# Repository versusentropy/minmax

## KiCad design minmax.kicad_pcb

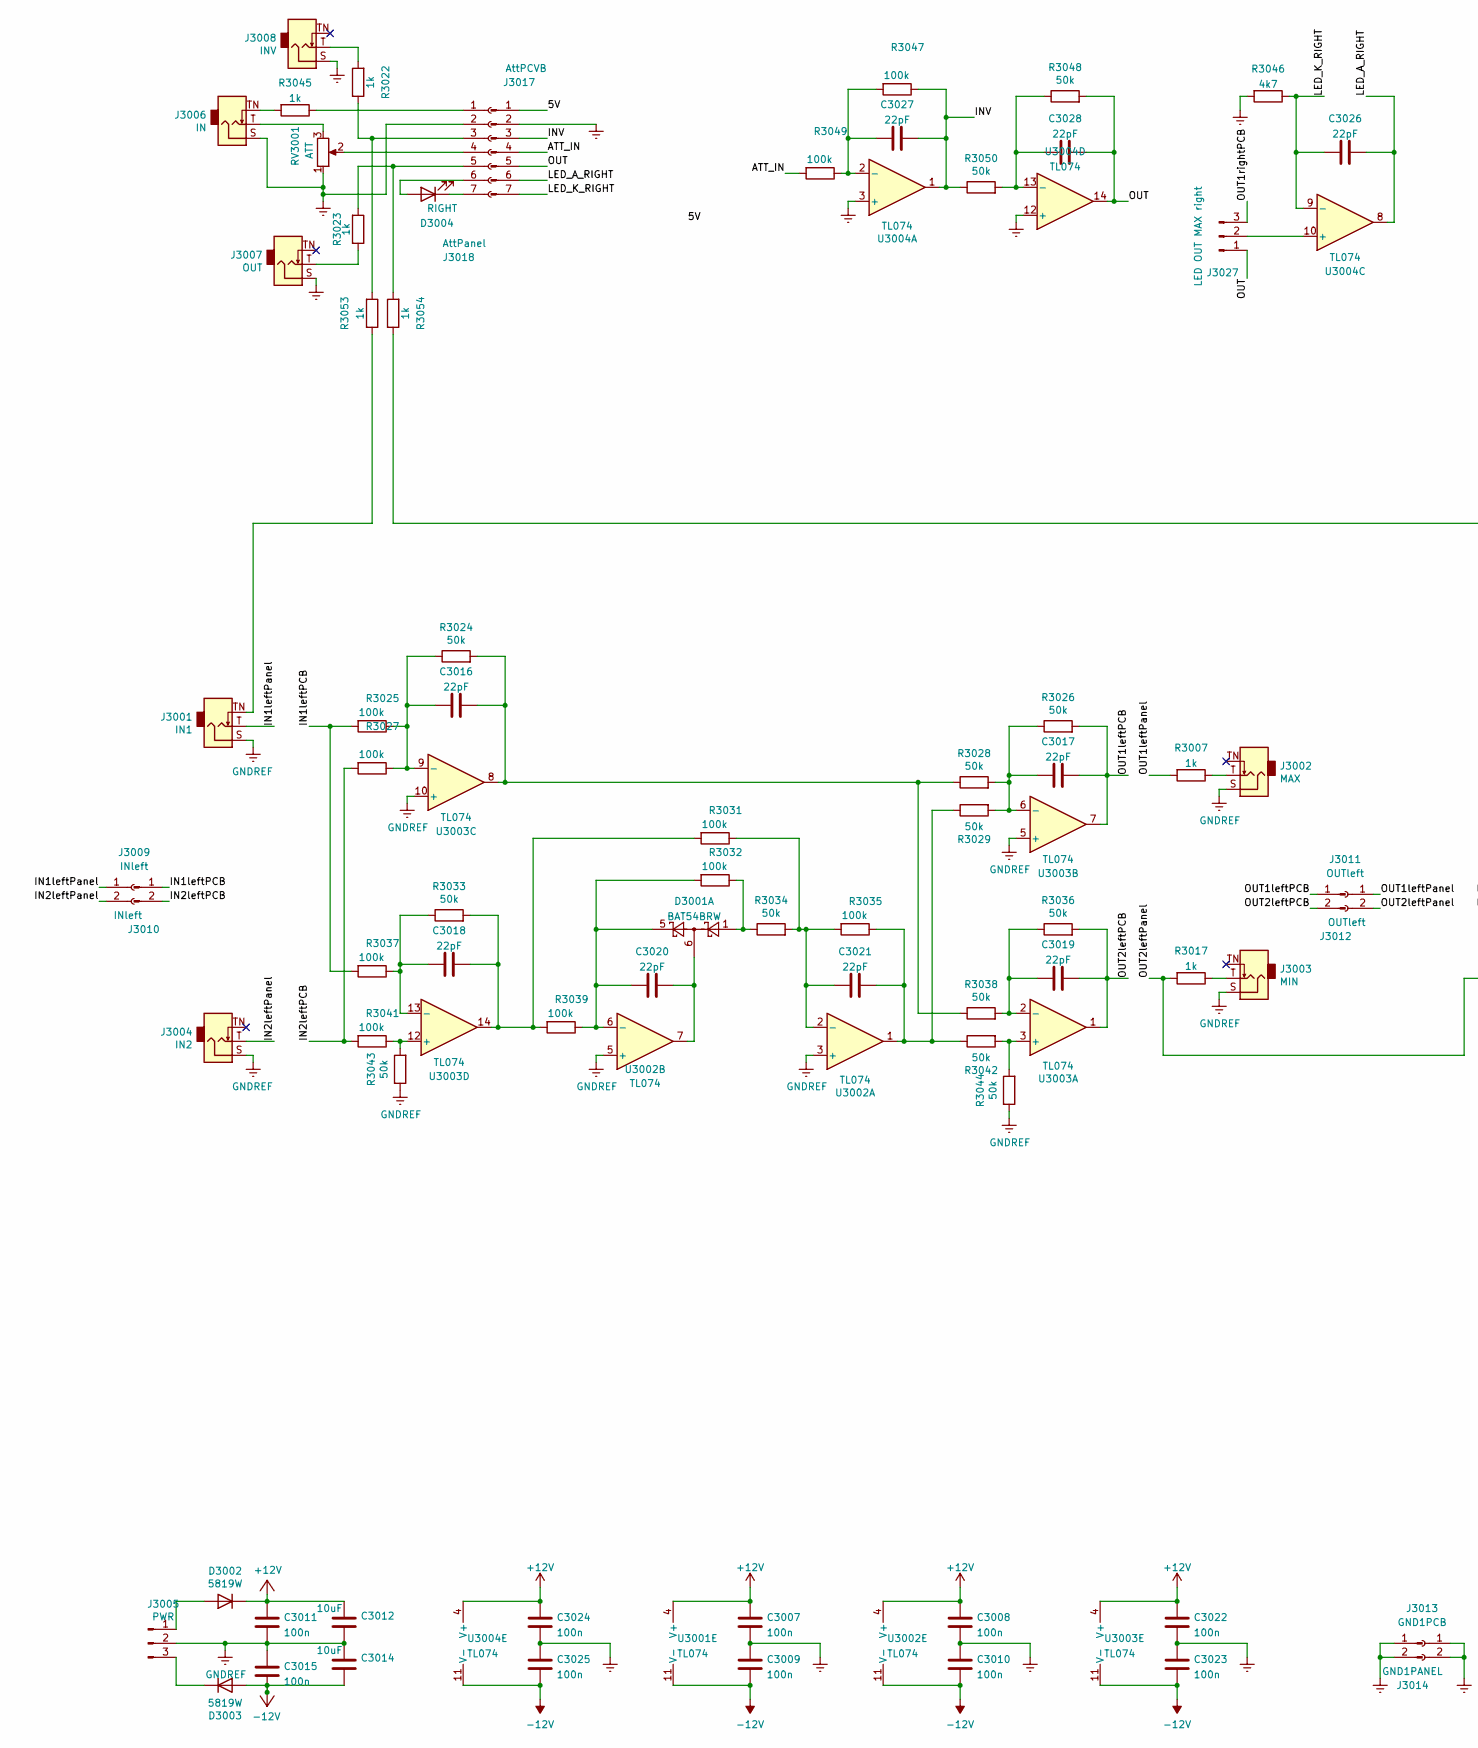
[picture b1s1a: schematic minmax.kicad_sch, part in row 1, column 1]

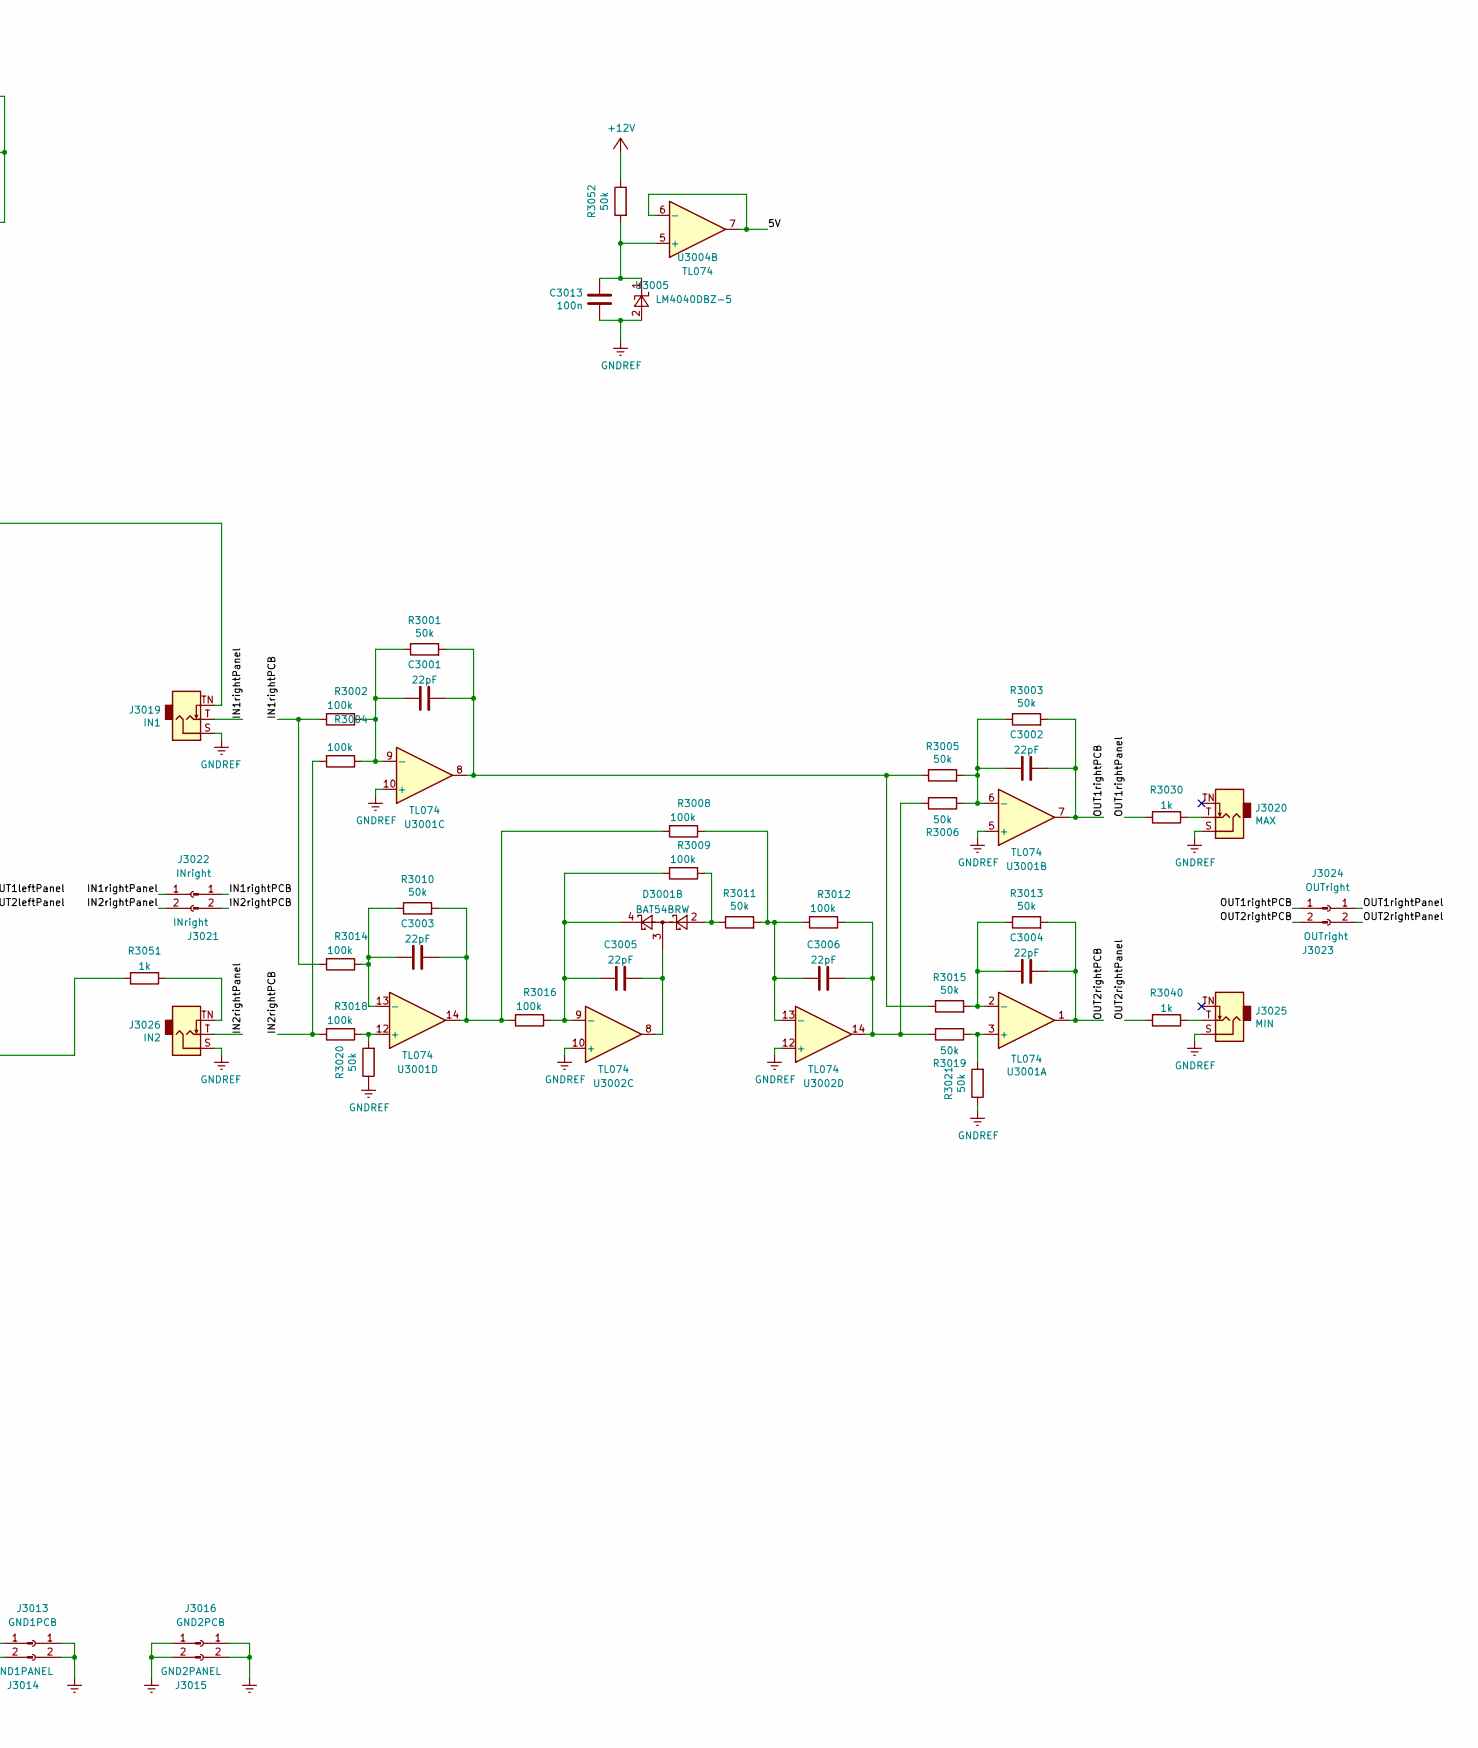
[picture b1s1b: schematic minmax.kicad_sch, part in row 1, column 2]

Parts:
C3001, C3002, C3003, C3004, C3005, C3006, C3016, C3017, C3018, C3019, C3020, C3021, C3026, C3027, C3028: 22pF; C_0402_1005Metric; LCSC C1555
C3007, C3008, C3009, C3010, C3011, C3013, C3015, C3022, C3023, C3024, C3025: 100n; C_0402_1005Metric; LCSC C307331
C3012, C3014: 10uF; C_0805_2012Metric; LCSC C15850
D3001: BAT54BRW; SOT-363_SC-70-6; LCSC C124897
D3002, D3003: 5819W; D_SOD-123; LCSC C8598
D3004: RIGHT; LED_D3.0mm
J3001, J3019: IN1; Jack_3.5mm_QingPu_WQP-PJ398SM_Vertical_CircularHolesSMALL
J3002, J3020: MAX; Jack_3.5mm_QingPu_WQP-PJ398SM_Vertical_CircularHolesSMALL
J3003, J3025: MIN; Jack_3.5mm_QingPu_WQP-PJ398SM_Vertical_CircularHolesSMALL
J3004, J3026: IN2; Jack_3.5mm_QingPu_WQP-PJ398SM_Vertical_CircularHolesSMALL
J3005: PWR; eurorac_power-v2
J3006: IN; Jack_3.5mm_QingPu_WQP-PJ398SM_Vertical_CircularHolesSMALL
J3007: OUT; Jack_3.5mm_QingPu_WQP-PJ398SM_Vertical_CircularHolesSMALL
J3008: INV; Jack_3.5mm_QingPu_WQP-PJ398SM_Vertical_CircularHolesSMALL
J3009: INleft; PinHeader_1x02_P2.54mm_Vertical
J3010: INleft; PinSocket_1x02_P2.54mm_Vertical
J3011: OUTleft; PinHeader_1x02_P2.54mm_Vertical
J3012: OUTleft; PinSocket_1x02_P2.54mm_Vertical
J3013: GND1PCB; PinHeader_1x02_P2.54mm_Vertical
J3014: GND1PANEL; PinSocket_1x02_P2.54mm_Vertical
J3015: GND2PANEL; PinSocket_1x02_P2.54mm_Vertical
J3016: GND2PCB; PinHeader_1x02_P2.54mm_Vertical
J3017: AttPCVB; PinHeader_1x07_P2.54mm_Vertical
J3018: AttPanel; PinSocket_1x07_P2.54mm_Vertical
J3021: INright; PinSocket_1x02_P2.54mm_Vertical
J3022: INright; PinHeader_1x02_P2.54mm_Vertical
J3023: OUTright; PinSocket_1x02_P2.54mm_Vertical
J3024: OUTright; PinHeader_1x02_P2.54mm_Vertical
J3027: LED OUT MAX right; PinHeader_1x03_P2.54mm_Vertical
R3001, R3003, R3005, R3006, R3010, R3011, R3013, R3015, R3019, R3020, R3021, R3024, R3026, R3028, R3029, R3033, R3034, R3036, R3038, R3042, R3043, R3044, R3048, R3050, R3052: 50k; R_0402_1005Metric; LCSC C25897
R3002, R3004, R3008, R3009, R3012, R3014, R3016, R3018, R3025, R3027, R3031, R3032, R3035, R3037, R3039, R3041, R3047, R3049: 100k; R_0402_1005Metric; LCSC C25741
R3007, R3017, R3022, R3023, R3030, R3040, R3045, R3051, R3053, R3054: 1k; R_0603_1608Metric; LCSC C21190
R3046: 4k7; R_0603_1608Metric; LCSC C23162
RV3001: ATT; RD901F-ALPHA-POT
U3001, U3002, U3003, U3004: TL074; TSSOP-14_4.4x5mm_P0.65mm; LCSC C96507
U3005: LM4040DBZ-5; SOT-23; LCSC C202168

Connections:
+12V: C3007.1, C3008.1, C3011.1, C3012.1, C3022.1, C3024.1, D3002.1 (K), R3052.1, U3001.4 (V+), U3002.4 (V+), U3003.4 (V+), U3004.4 (V+)
-12V: C3009.2, C3010.2, C3014.2, C3015.2, C3023.2, C3025.2, D3003.2 (A), U3001.11 (V-), U3002.11 (V-), U3003.11 (V-), U3004.11 (V-)
/5V: J3017.1, U3004.6 (-), U3004.7
/ATT_IN: J3017.4, R3049.2
/IN1leftPCB: J3009.1, R3025.2, R3037.2
/IN1leftPanel: J3001.T, J3010.1
/IN1rightPCB: J3022.1, R3002.2, R3014.2
/IN1rightPanel: J3019.T, J3021.1
/IN2leftPCB: J3009.2, R3027.2, R3041.2
/IN2leftPanel: J3004.T, J3010.2
/IN2rightPCB: J3022.2, R3004.2, R3018.2
/IN2rightPanel: J3021.2, J3026.T
/INV: C3027.2, J3017.3, R3047.1, R3050.1, U3004.1
/LED_A_RIGHT: C3026.2, J3017.6, U3004.8
/LED_K_RIGHT: C3026.1, J3017.7, R3046.1, U3004.9 (-)
/OUT: C3028.2, J3017.5, J3027.1, R3048.2, U3004.14
/OUT1leftPCB: C3017.2, J3011.1, R3026.2, U3003.7
/OUT1leftPanel: J3012.1, R3007.2
/OUT1rightPCB: C3002.2, J3024.1, J3027.3, R3003.2, U3001.7
/OUT1rightPanel: J3023.1, R3030.2
/OUT2leftPCB: C3019.2, J3011.2, R3036.2, U3003.1
/OUT2leftPanel: J3012.2, R3017.2, R3051.2
/OUT2rightPCB: C3004.2, J3024.2, R3013.2, U3001.1
/OUT2rightPanel: J3023.2, R3040.2
GNDREF: C3007.2, C3008.2, C3009.1, C3010.1, C3011.2, C3012.2, C3013.1, C3014.1, C3015.1, C3022.2, C3023.1, C3024.2, C3025.1, J3001.S, J3002.S, J3003.S, J3004.S, J3005.2, J3006.S, J3007.S, J3008.S, J3013.1, J3013.2, J3014.1, J3014.2, J3015.1, J3015.2, J3016.1, J3016.2, J3017.2, J3018.2, J3019.S, J3020.S, J3025.S, J3026.S, R3020.1, R3021.1, R3043.1, R3044.1, R3046.2, RV3001.1, U3001.5 (+), U3001.10 (+), U3002.3 (+), U3002.5 (+), U3002.10 (+), U3002.12 (+), U3003.5 (+), U3003.10 (+), U3004.3 (+), U3004.12 (+), U3005.2 (A)
unnamed: C3001.1, R3001.1, R3002.1, R3004.1, U3001.9 (-)
unnamed: C3001.2, R3001.2, R3005.1, R3015.1, U3001.8
unnamed: C3002.1, R3003.1, R3005.2, R3006.2, U3001.6 (-)
unnamed: C3003.1, R3010.1, R3014.1, U3001.13 (-)
unnamed: C3003.2, R3008.2, R3010.2, R3016.2, U3001.14
unnamed: C3004.1, R3013.1, R3015.2, U3001.2 (-)
unnamed: C3005.1, D3001.4, R3009.2, R3016.1, U3002.9 (-)
unnamed: C3005.2, D3001.3, U3002.8
unnamed: C3006.1, R3008.1, R3011.2, R3012.2, U3002.13 (-)
unnamed: C3006.2, R3006.1, R3012.1, R3019.1, U3002.14
unnamed: C3013.2, R3052.2, U3004.5 (+), U3005.1 (K)
unnamed: C3016.1, R3024.1, R3025.1, R3027.1, U3003.9 (-)
unnamed: C3016.2, R3024.2, R3028.1, R3038.1, U3003.8
unnamed: C3017.1, R3026.1, R3028.2, R3029.2, U3003.6 (-)
unnamed: C3018.1, R3033.1, R3037.1, U3003.13 (-)
unnamed: C3018.2, R3031.2, R3033.2, R3039.2, U3003.14
unnamed: C3019.1, R3036.1, R3038.2, U3003.2 (-)
unnamed: C3020.1, D3001.5, R3032.2, R3039.1, U3002.6 (-)
unnamed: C3020.2, D3001.6, U3002.7
unnamed: C3021.1, R3031.1, R3034.2, R3035.2, U3002.2 (-)
unnamed: C3021.2, R3029.1, R3035.1, R3042.1, U3002.1
unnamed: C3027.1, R3047.2, R3049.1, U3004.2 (-)
unnamed: C3028.1, R3048.1, R3050.2, U3004.13 (-)
unnamed: D3001.1, R3032.1, R3034.1
unnamed: D3001.2, R3009.1, R3011.1
unnamed: D3002.2 (A), J3005.1
unnamed: D3003.1 (K), J3005.3
unnamed: D3004.1 (K), J3018.7
unnamed: D3004.2 (A), J3018.6
unnamed: J3001.TN, R3053.1
unnamed: J3002.T, R3007.1
unnamed: J3003.T, R3017.1
unnamed: J3006.T, RV3001.3
unnamed: J3006.TN, R3045.2
unnamed: J3007.T, R3023.1
unnamed: J3008.T, R3022.2
unnamed: J3018.1, R3045.1
unnamed: J3018.3, R3022.1, R3053.2
unnamed: J3018.4, RV3001.2
unnamed: J3018.5, R3023.2, R3054.2
unnamed: J3019.TN, R3054.1
unnamed: J3020.T, R3030.1
unnamed: J3025.T, R3040.1
unnamed: J3026.TN, R3051.1
unnamed: J3027.2, U3004.10 (+)
unnamed: R3018.1, R3020.2, U3001.12 (+)
unnamed: R3019.2, R3021.2, U3001.3 (+)
unnamed: R3041.1, R3043.2, U3003.12 (+)
unnamed: R3042.2, R3044.2, U3003.3 (+)

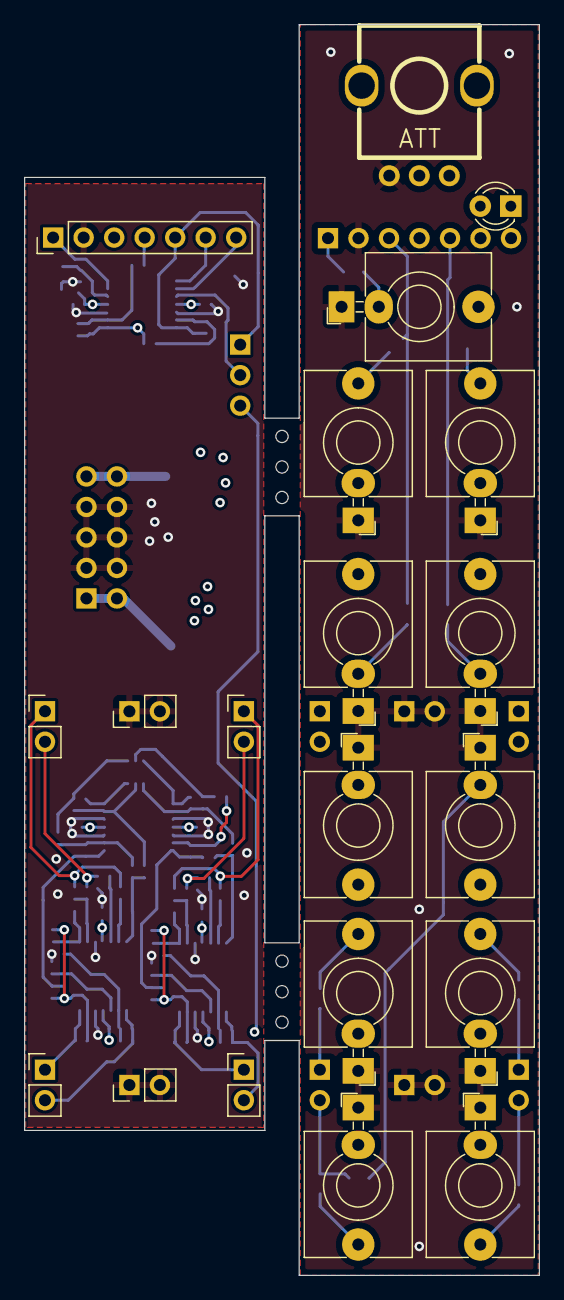
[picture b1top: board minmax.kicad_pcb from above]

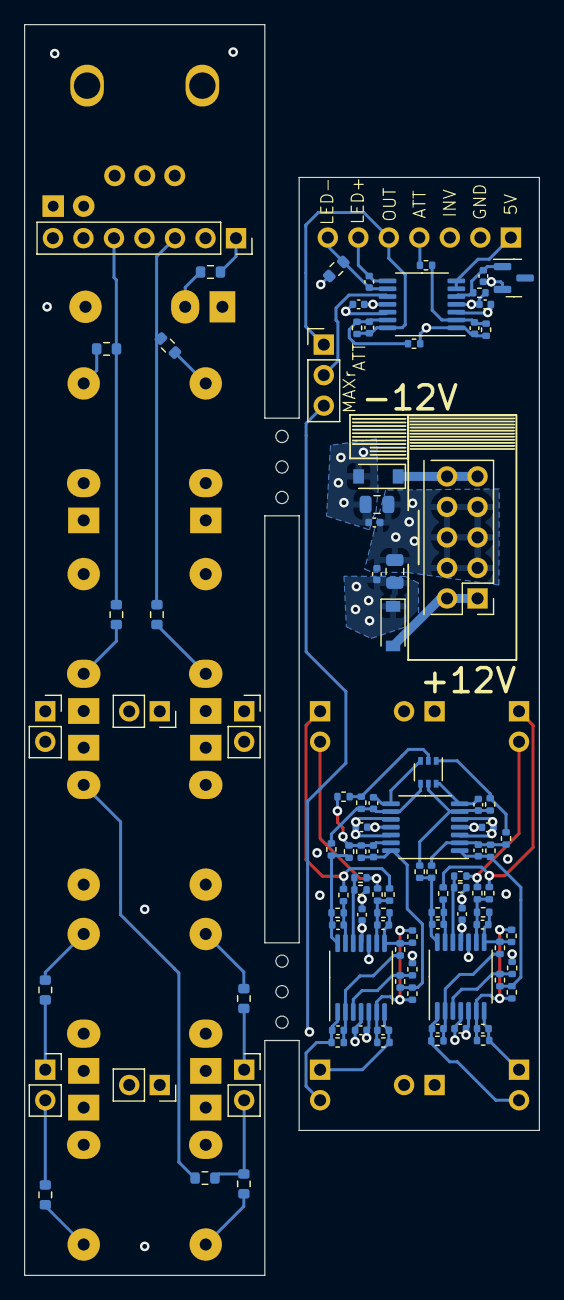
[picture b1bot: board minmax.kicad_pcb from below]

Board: 4 copper layers, 42.9 x 104.1 mm, 119 parts (99 on the bottom side), 74 nets.
